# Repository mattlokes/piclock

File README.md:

WordClock
=======

RGB Colour Word Clock, Powered by a Raspberry Pi/Similar Embedded Linux Board with matrix display capabilities.

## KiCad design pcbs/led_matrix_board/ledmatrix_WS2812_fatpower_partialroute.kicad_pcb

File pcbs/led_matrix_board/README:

This KICAD library is required for the PLCC6 footprint

https://github.com/open-project/kicadlibrary.git

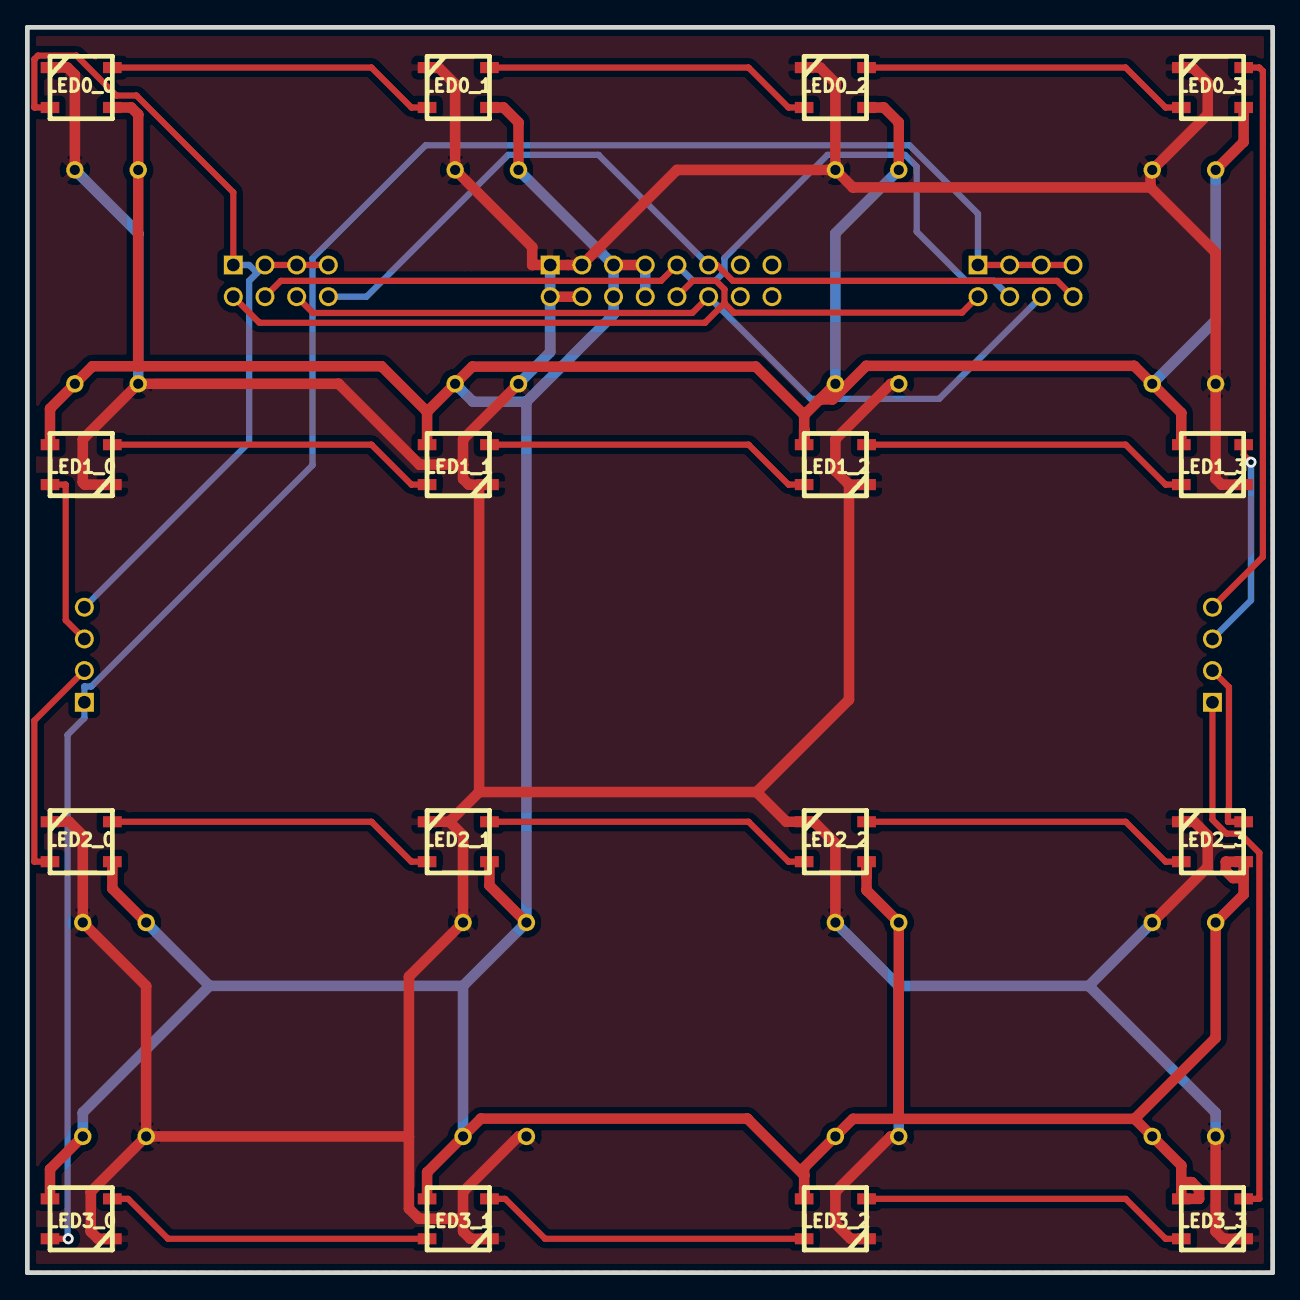
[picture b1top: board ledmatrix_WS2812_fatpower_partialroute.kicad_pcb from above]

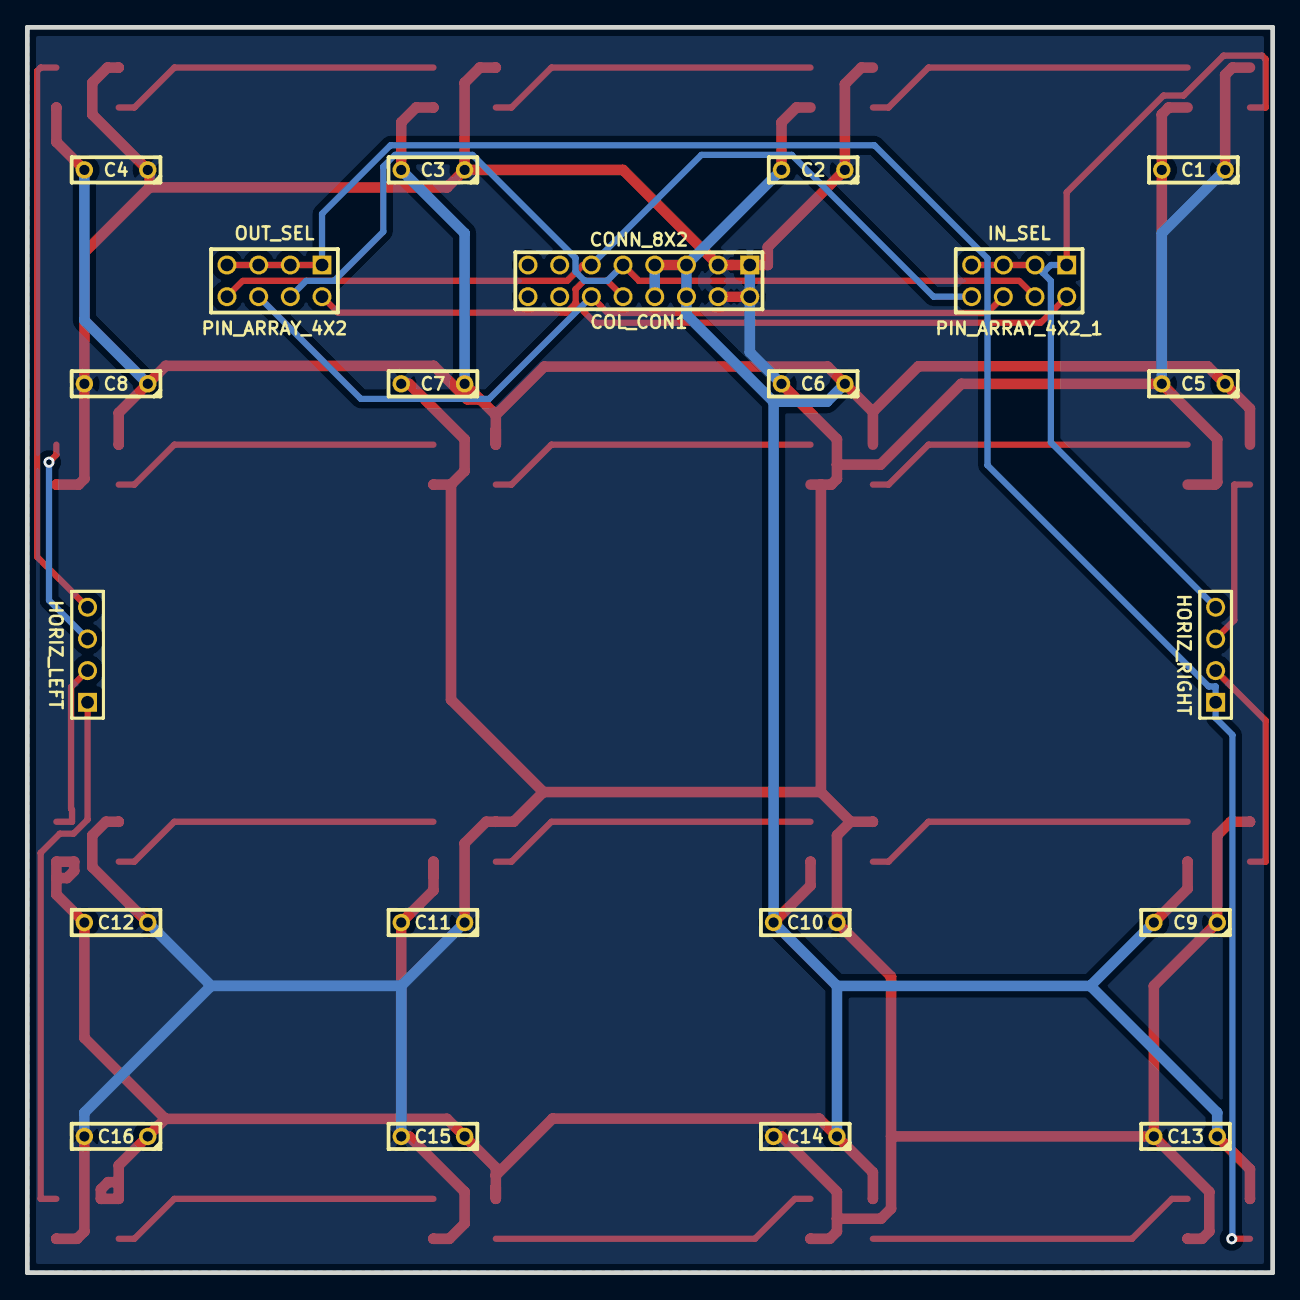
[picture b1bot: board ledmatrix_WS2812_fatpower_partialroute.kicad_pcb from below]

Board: 2 copper layers, 99.8 x 99.8 mm, 37 parts (21 on the bottom side), 26 nets.

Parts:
C1: C104; C2
C2, C3, C4, C5, C6, C7, C8, C9, C10, C11, C12, C13, C14, C15, C16: C***; C2
COL_CON1: CONN_8X2; pin_array_8x2
HORIZ_LEFT: CONN_4; PIN_ARRAY_4x1
HORIZ_RIGHT: CONN_4; PIN_ARRAY_4x1
LED0_0, LED0_1, LED0_2, LED0_3, LED1_0, LED1_1, LED1_2, LED1_3, LED2_0, LED2_1, LED2_2, LED2_3, LED3_0, LED3_1, LED3_2, LED3_3: RGB_LED_AVAGO; RGB_LED_PLCC6
PIN_ARRAY_4X2: OUT_SEL; pin_array_4x2
PIN_ARRAY_4X2_1: IN_SEL; pin_array_4x2

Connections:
unnamed: C1.2, C2.2, C3.2, C4.2, C5.1, C6.1, C7.1, C8.1, C9.2, C10.2, C11.2, C12.2, C13.1, C14.1, C15.1, C16.1, COL_CON1.5, COL_CON1.6, COL_CON1.7, COL_CON1.8, LED0_0.1, LED0_1.1, LED0_2.1, LED0_3.1, LED1_0.1, LED1_1.1, LED1_2.1, LED1_3.1, LED2_0.1, LED2_1.1, LED2_2.1, LED2_3.1, LED3_0.1, LED3_1.1, LED3_2.1, LED3_3.1
unnamed: C1.1, C2.1, C3.1, C4.1, C5.2, C6.2, C7.2, C8.2, C9.1, C10.1, C11.1, C12.1, C13.2, C14.2, C15.2, C16.2, COL_CON1.1, COL_CON1.2, COL_CON1.3, COL_CON1.4, LED0_0.6, LED0_1.6, LED0_2.6, LED0_3.6, LED1_0.6, LED1_1.6, LED1_2.6, LED1_3.6, LED2_0.6, LED2_1.6, LED2_2.6, LED2_3.6, LED3_0.6, LED3_1.6, LED3_2.6, LED3_3.6
unnamed: HORIZ_RIGHT.4, LED0_0.2, PIN_ARRAY_4X2_1.1, PIN_ARRAY_4X2_1.3, PIN_ARRAY_4X2_1.5, PIN_ARRAY_4X2_1.7
unnamed: COL_CON1.10, PIN_ARRAY_4X2.2, PIN_ARRAY_4X2_1.2
unnamed: COL_CON1.9, PIN_ARRAY_4X2.4, PIN_ARRAY_4X2_1.4
unnamed: COL_CON1.12, PIN_ARRAY_4X2.6, PIN_ARRAY_4X2_1.6
unnamed: COL_CON1.11, PIN_ARRAY_4X2.8, PIN_ARRAY_4X2_1.8
unnamed: LED0_0.5, LED0_1.2
unnamed: LED0_1.5, LED0_2.2
unnamed: LED0_2.5, LED0_3.2
unnamed: HORIZ_LEFT.4, LED0_3.5
unnamed: HORIZ_LEFT.3, LED1_3.2
unnamed: LED1_2.2, LED1_3.5
unnamed: LED1_1.2, LED1_2.5
unnamed: LED1_0.2, LED1_1.5
unnamed: HORIZ_RIGHT.3, LED1_0.5
unnamed: HORIZ_RIGHT.2, LED2_0.2
unnamed: LED2_0.5, LED2_1.2
unnamed: LED2_1.5, LED2_2.2
unnamed: LED2_2.5, LED2_3.2
unnamed: HORIZ_LEFT.2, LED2_3.5
unnamed: HORIZ_LEFT.1, LED3_3.2
unnamed: LED3_2.2, LED3_3.5
unnamed: LED3_1.2, LED3_2.5
unnamed: LED3_0.2, LED3_1.5
unnamed: HORIZ_RIGHT.1, LED3_0.5, PIN_ARRAY_4X2.1, PIN_ARRAY_4X2.3, PIN_ARRAY_4X2.5, PIN_ARRAY_4X2.7

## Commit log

2013-04-05 Setting Up Repo
2013-04-05 tidying up
2013-04-05 Created virtual grid, which reads in config from grid.conf then generates a piclock simulation
2013-04-05 Add initial documentation to repo
2013-04-06 Create sim scripts and Create GridInterface_Sim file structure
2013-04-07 Seperate Threaded GUI Window with command queue interface, basic clear and set pixel functions implemented, basic test working
2013-04-07 Seperate Threaded GUI Window with command queue interface, basic clear and set pixel functions implemented, basic test working2
2013-04-07 Add GridWordDef.py , which contains pixel mappings to words need for time
2013-04-07 Add function placeholder for printing the time
2013-04-07 Fully working wordclock functionality with simulator, needs commenting and tidying up, but seems to work
2013-04-07 Bugfix for the time at "o\'clock\'
2013-04-07 Bugfix for minutes being less that 10
2013-04-07 Bugfix for quarter past the hour
2013-04-07 rearranged grid to make eighteen look better, and added the time of the time function in.
2013-05-27 Added STM32 Code Make Files and Libraries. Minigrid added.
2013-05-27 Add Drill Template SVG
2013-05-28 Got Indiviual LED Control, Current code dims one row of LEDs
2014-07-16 Adding pic32 code for full system
2014-07-16 Removing Old STM code used for very first prototype
2014-07-16 Add LED Driver board PCB Eagle files and Gerbers
2014-07-16 Added 3D Printed Parts SCAD and STL files, As well as Kicad Ledmatrix designs with Gerbers
2014-11-28 Add Python Scripts for communicating with the PIC32
2014-11-28 Add Hex Snapshots of working Code
2014-11-29 Rename directory
2014-11-29 Start Creating Python Framework, add clockApp
2014-11-29 Add hwInterface to render frames on the LED Grid
2014-11-30 Add Component Glue Function main.py
2014-11-30 Fix mins to Bug, Cleanup Exit code, fix syntax bugs. Working
2014-11-30 Add Websocket Control Module
2014-11-30 Update Clock Application to decode commands
2014-11-30 Add Initial Pages to send Commands
2014-11-30 add WebSocket Interface to system
2014-12-04 Update of all PIC32 Code, current works using DMA to read UART Data
2014-12-04 Tidy PIC32 Code up
2014-12-04 Add fastRx mode to hwInterface to allow lower cpu usage and faster uart rx
2014-12-05 Cleanup webpages and improve cpu usage
2014-12-10 Join Cmd and Frame Queues and use Get properly to save CPU usage
2014-12-10 Fix Minor Bugs
2014-12-10 Add fakeSerial switch to allow simulations of the clock without plugging it in
2014-12-11 Add Digital Clock Mode for ClockApp
2014-12-12 Add Mega Clock Mode
2014-12-12 rework system directory structure and covert frameLib to a proper static class
2014-12-12 more system rework
2014-12-12 Move clockAppConsts toa seperate file
2014-12-12 Move Consts out of Clock App into seperate file
2014-12-12 Add Git Ignore File
2014-12-13 Move webserver content around
2014-12-13 Move More webserver content around, create webserver python wrapper, create colourTestApp
2014-12-13 Add CreateColourFrame function frameLibrary, and edit webserver config
2014-12-13 Split lighttpd config file into PC and PI versions
2014-12-13 Fixing ser instantiation to be self.ser.
2014-12-13 add webserver temp directory to the ignore file
2014-12-13 add Vertical Line Animation
2014-12-14 Make Vertical Line Animation More interesting and faster
2014-12-21 Add Colour Translation Table
2014-12-24 Create Module Instantiation Loop & Message Routing Prototype
2014-12-24 Lower CPU Usage and small changes
2014-12-27 Tidy Up Webpage Libraries
2014-12-27 Update Webpage Structure and python webserver module
2014-12-27 add more ignores to .gitignore
2014-12-27 Add Basic Colour NonLinearity correction
2014-12-27 Changes due to repo rename and main tidy up
2014-12-28 Fix Kill behaviour, to close down safetly, Add system print class to print nicely formatted messages, Add rxQueue to wsInterface and tidy various bits up
2014-12-28 Add Status Page Template, Fix ClockApp Wepbage as well as tidying up navigation menu.
2014-12-28 Update ClockApp and Webpage to add controls and handling, Fix One Minute Bug
2014-12-29 Add Pause and Resume to Applications
2014-12-29 NEW APPLICATION HANDLING, use applciation object to help with code resuse
2014-12-29 Add ColourTestApp Page and add application switching mechanism
2014-12-31 Pi Fixes
2015-01-02 Add Get Pixel Value Function to frameLib
2015-01-02 Add Snake Application
2015-01-02 Fix Snake App Html Page
2015-07-23 Fix Html Pages to use server IP for websocket rather than fixed
2015-07-26 Fix SnakeApp Button Style
2015-07-26 Initial Changes to get WS2812b LED interface working on PIC32
2015-07-26 Add WS2812b LED PCBS
2015-08-02 Attempted Fix for SFP Error (Suspected None Atomic access between threads)
2015-08-02 Snake Control Fix
2015-08-03 Add Clock Transitions
2015-08-04 Add platform argument to allow webserver to run on diffrent platform configs
2015-08-04 Add Shift Frame Functions in frameLib, and clean up Clock Transitions
2015-08-04 Implemented VSlide Clock Transition
2015-08-10 Support for WS2812B matrix only
2015-09-05 Structure overhaul, abandon dodgy Python threading and use ZeroMQ for communications between interfaces and applications
2015-09-05 Further Restructure, all Applications and interfaces updated
2015-09-07 Finish ZeroMQ rework, System working, still need to right C hardware interface
2015-09-08 Add Python Hardware Component
2015-09-24 Update to latest everything
2015-09-24 Add New direct Raspberry Pi WS2812 driving C code
2015-09-24 Direct LED Raspberry Pi interface working, need to fix colours though
2015-09-24 Fix all the Colour Ordering between the LED interface adn the python modules
2015-09-29 updated temporary run script
2015-09-29 clockapp: Add Horizontal Slide Transition and framework for other transitions
2015-10-01 Add Fade Clock Transition
2015-10-03 Flip Clock 180 degrees as its now *upside down*
2015-10-05 Repo Cleanup
2015-12-15 Bring Repo upto Date with Clock
2015-12-15 Add ws2812b ledInterface Binary
2015-12-16 Updated Install scripts to contain all dependancies
2015-12-18 Create Notifiers Placeholder
2016-03-03 Raspbian Jessie Support, ZMQ fixes and install script
2016-03-04 Systemd Service Support; Rework webserver and ledDisplay startup; Rework lighttpd config file; Implement Install script
2016-03-05 Repo Tidy Up
2016-03-11 Overhaul Clock Control Page, to use JQUERY events rather than ineffecient timer method
2016-03-11 Further ClockApp Webpage Cleanup
2016-03-11 Add Keyboard Controls to Snake
2016-03-11 Fix FrameLib Colour Definition
2016-03-12 Add Websocket msg tx from Server to Client, Return Application state to the client to keep interface in sync with internal state
2016-09-18 Updates to install script
2017-08-26 Add new webDisplay that simulates clock face in the browser, also tidy up displays directory, each display has own directory.
